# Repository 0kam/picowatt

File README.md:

# picowatt

Raspberry Pi Pico 2 + INA228 による PPK2 ライクな消費電力測定システム。

## クイックスタート

### リリース版を使う(推奨)

1. **ファームウェア**: [Releases](https://github.com/0kam/picowatt/releases) から
   `picowatt-vX.Y.Z.uf2` をダウンロードし、BOOTSEL ボタンを押しながら Pico 2 を
   USB 接続して現れる `RP2350` ドライブにドラッグ(または
   `picotool load -fx picowatt-vX.Y.Z.uf2`)。
2. **PC アプリ**: [uv](https://docs.astral.sh/uv/) があれば1行で起動できる:

   ```sh
   uvx picowatt        # GUI
   uvx --from picowatt picowatt-cli --seconds 10 --csv out.csv
   ```

   (pip 派は `pipx install picowatt` でも可)

### ソースからのビルドと書き込み

必要なもの: cmake、ARM GNU toolchain、[pico-sdk](https://github.com/raspberrypi/pico-sdk) 2.3+(`lib/tinyusb` サブモジュール込み)、picotool 2.3+。

```sh
export PICO_SDK_PATH=~/pico-sdk            # 既定値
export PICO_TOOLCHAIN_PATH=~/toolchains/arm-gnu-toolchain-...  # PATH に無い場合
./firmware/build.sh                        # → firmware/build/picowatt.uf2

# 初回のみ BOOTSEL ボタンを押しながら USB 接続して:
picotool load -fx firmware/build/picowatt.uf2
# 2回目以降はボタン不要(実行中ファームがリブートコマンドを受け付ける)
```

UF2 ドライブへのドラッグ&ドロップでも書き込めるが、USB マスストレージが
制限された環境では picotool 経由(PICOBOOT)が使える。

### PC アプリ

```sh
cd app
uv sync
uv run picowatt        # GUI
uv run picowatt-cli --seconds 10 --csv out.csv   # ヘッドレスキャプチャ
```

GUI: Connect → Start でストリーミング開始。Measure チェックで電力プロット上の
任意区間を選択して Wh/Ah を積算。Log CSV… で全サンプルをファイルに記録。
Calibrate… でゼロ校正・1点ゲイン校正(ボードIDごとに自動保存され、接続時に
自動適用)。プロトコル仕様は [docs/protocol.md](docs/protocol.md)、実測性能は
[docs/verification.md](docs/verification.md) を参照。値がおかしいときは
[docs/troubleshooting.md](docs/troubleshooting.md)（症状から引ける）。

## 概要

INA228 電力モニタを Pico 2 で読み取り、USB シリアル経由で PC に転送。PC 側アプリでリアルタイム表示・ロギング・任意区間の電力量(Wh)積算を行う。

対応する測定モード:

- **消費電力測定** — 機器の消費電力を INA228 1枚で測定
- **DC-DC 効率測定** — INA228 2枚で入出力を同時測定し、効率を算出

## ハードウェア構成

| 役割 | 型番 | 備考 |
|---|---|---|
| MCU | Raspberry Pi Pico 2 (RP2350) | USB CDC で PC 接続 |
| 電力モニタ | Adafruit INA228 ×2 | 15mΩ 0.1% シャント搭載、20bit ADC |
| ディスプレイ | SSD1306 128×64 I2C OLED | 秋月 |
| 電源 | アズワン PS30V5A10 | 0-30V / 0-5A |
| 電子負荷 | ET5410A+ | 効率測定時の負荷掃引用 |

### I2C アドレス

| デバイス | アドレス | 設定 |
|---|---|---|
| SSD1306 OLED | `0x3C` | — |
| INA228 #1 (入力側) | `0x40` | デフォルト |
| INA228 #2 (出力側) | `0x41` | 基板裏 A0 ジャンパを閉 |

### 結線

ロジック側は I2C0 バスに全デバイスをぶら下げる。ブレッドボード配線の代わりに
キャリア基板を起こす場合は [hardware/](hardware/README.md) を参照(KiCad プロジェクト)。

| Pico 2 | 接続先 |
|---|---|
| 3V3 OUT (pin 36) | INA228 ×2 VIN / OLED VCC |
| GND (pin 38) | INA228 ×2 GND / OLED GND / 電源 − (1点のみ) |
| GP4 (pin 6) SDA | INA228 ×2 SDA / OLED SDA |
| GP5 (pin 7) SCL | INA228 ×2 SCL / OLED SCL |

I2C プルアップは INA228 基板の 10kΩ が効くため追加不要。

ブレッドボードで組む場合の全体図（ロジック配線 + 電源経路）:

電力ラインはハイサイド測定。**基板裏の VBus ジャンパを閉じる**(VBUS が VIN+ に接続され、ハイサイド構成になる)。

```
電源(+) → #1 VIN+ ─[15mΩ]─ #1 VIN− → DUT(+)
電源(−) ←──────────────────────────── DUT(−)
```

キャリア基板でのつなぎ方（赤 = ＋側、青 = −側。USB が左、端子台が上辺）:

効率測定時は出力側に #2 を追加:

```
DUT出力(+) → #2 VIN+ ─[15mΩ]─ #2 VIN− → 電子負荷(+)
DUT出力(−) ←───────────────────────────── 電子負荷(−)
```

ch1 用の INA228 は裏の A0 ジャンパを閉じて右の J3 に挿す。詳細は
[hardware/README.md](hardware/README.md#使い方配線図)。

**電源の − は必ず picowatt の GND（キャリア基板なら J5）に繋ぐ。** INA228 は
バス電圧を自分の GND ピン基準で測るので、この 1 本が無いと基板が電源系から
浮き、VBUS が 0 V と −数十 V の間を 50/60 Hz で振動する（実在しない電圧）。
GUI はステータスバー右端に赤字の警告を出し、`picowatt-cli` は
`WARNING: bus voltage goes negative` を出す。図解は [docs/troubleshooting.md](docs/troubleshooting.md)。

GND の共通接続は 1 点のみ。複数箇所で接続するとループになる。

## キャリブレーション

INA228 は `SHUNT_CAL` レジスタ (0x02) にシャント値とフルスケールから決まる係数を書き込む必要がある。

```
CURRENT_LSB = 最大期待電流 / 2^19
SHUNT_CAL   = 13107.2e6 × CURRENT_LSB × R_SHUNT
```

`R_SHUNT = 0.015` (Adafruit ボード搭載値)。

デフォルト設定 (3A 想定, ADCRANGE=0 / ±163.84mV):

```
CURRENT_LSB = 8e-6        # 8 µA/LSB, フルスケール約 4.19A
SHUNT_CAL   = 1573
```

低電流モード (ADCRANGE=1 / ±40.96mV) では CURRENT_LSB を 1/4 に下げて分解能を上げる。
ADCRANGE=1 では **SHUNT_CAL の計算値を 4 倍**する必要があるが、LSB の 1/4 と相殺して
レジスタ値は同じになる:

```
CURRENT_LSB = 2e-6        # 2 µA/LSB, フルスケール約 1.05A
SHUNT_CAL   = 1573        # = 4 × 13107.2e6 × 2e-6 × 0.015
```

出荷時のシャント実値は公称から数%ずれることがあるため、既知電流での 1 点校正を推奨。

## 機能要件

### ファームウェア (Pico 2)

- INA228 ×2 の初期化・設定変更 (ADCRANGE, 変換時間, 平均化回数)
- 定期サンプリングと USB シリアルへのストリーミング
- OLED へのリアルタイム数値表示
- PC からのコマンド受信 (レンジ切替、サンプリングレート変更、ゼロ校正、モード切替)
- I2C は 400kHz 以上 (Pico 2 は 1MHz まで可)

### PC アプリ

- シリアル接続とリアルタイムグラフ表示 (電圧 / 電流 / 電力)
- CSV ロギング
- **表示中の任意範囲を選択して電力量(Wh)を積算**
- 効率モード時は入出力電力と効率(%)を同時表示
- 測定設定の変更 UI

## 想定サンプリングレート

I2C 経由のため PPK2 (100kSa/s) 相当は狙わない。数百 Hz〜数 kHz を目標。変換時間と平均化回数の設定でノイズと速度をトレードオフする。

## 参考

- [Adafruit INA228 Learn Guide](https://learn.adafruit.com/adafruit-ina228-i2c-power-monitor)
- INA228 データシート (TI)

## ライセンス

GPL-3.0 — 詳細は [LICENSE](LICENSE) を参照。

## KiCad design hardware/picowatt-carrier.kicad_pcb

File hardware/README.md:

# picowatt キャリア基板

Pico 2 + INA228 ×2 + SSD1306 OLED を 1 枚に載せるキャリア基板。ロジックはすべて
I2C0 にぶら下がるだけなので、この基板は **電源と I2C を配るだけ** で能動素子を持たない。

- 基板サイズ **92 × 70 mm**（2 層、厚さ 1.6mm）。100×100mm 以内なので各社の最安枠に収まる
- 子基板（Pico 2 / INA228 ×2 / OLED）はすべて 2.54mm ソケットで着脱可能
- 高さはすべて **11.0mm の同一面** に揃う（ソケットのハウジング高さ 8.5mm +
  ピンヘッダのハウジング厚み 2.5mm、いずれも秋月の仕様値）

KiCad 10 で `picowatt-carrier.kicad_pro` を開く。シンボルとフットプリントのうち
本基板固有のものは `picowatt.kicad_sym` / `picowatt.pretty/` にプロジェクト内蔵。
残りは KiCad 標準ライブラリを参照する。

> KiCad を一度も起動していない環境ではグローバルライブラリテーブルが未作成のため、
> 標準ライブラリ参照がエラーになる。KiCad を一度起動すれば自動生成される。

## 配置の考え方

配線の向きを 3 方向に分離してある。

| 方向 | 出ていくもの |
|---|---|
| 上辺（奥） | INA228 ×2 のネジ端子台、GND 端子台 — 太い電源線はすべて奥へ |
| 左辺 | Pico 2 の Micro-USB B — PC へ |
| 手前 | OLED の表示面 |

INA228 の端子台が基板の外を向くので、電源線は基板の上を這わない。

J5 (GND 端子台) も同じ向きに揃えるため **180° 回転して配置してある。** TB007-508 の
機械図面 (SECTION A-A) では、ピン列は電線挿入面ではなく**背面から 4.90mm**（挿入面からは
5.35mm）の位置にある。回転 0 のままだと電線が手前から入り、基板の上をまたぐことになる。

## 回路

ネットは 6 本だけ。

| ネット | 接続先 |
|---|---|
| `+3V3` | Pico 2 pin36 (3V3 OUT) → INA228 ×2 の VIN、OLED VDD、プルアップ、パスコン |
| `GND` | Pico 2 の GND 群、各子基板 GND、GND 端子台、TP1 |
| `SDA` | Pico 2 GP4 (pin 6) → INA228 ×2、OLED |
| `SCL` | Pico 2 GP5 (pin 7) → INA228 ×2、OLED |
| `ALRT0` | Pico 2 GP6 (pin 9) → INA228 ch0 の ALRT |
| `ALRT1` | Pico 2 GP7 (pin 10) → INA228 ch1 の ALRT |

`ALRT0` / `ALRT1` は現ファームウェアでは未使用だが、`firmware/src/config.h` が
GP6/GP7 を予約済みで配線コストがゼロなので引いてある。INA228 側の ALRT は
オープンドレインなのに基板上にプルアップが無いため、R1/R2 (10kΩ) を本基板に載せる。

I2C プルアップは INA228 が各 10kΩ を持ち、2 枚並列で 5kΩ、さらに OLED モジュール分も
乗るので追加不要と判断した。R3/R4 は**未実装** (DNP) のパッドとして用意してあるだけで、
1MHz で波形が鈍る場合にのみ実装する。

### 電力ラインは基板に通さない

INA228 の 2.54mm ヘッダには `VBUS` / `VIN-` / `VIN+` も出ているが、**基板側は無接続**に
してある（J2/J3 の pin 5,6,7）。最大 5A の電力ラインをキャリア基板に通す理由がないため、
電源線は従来通り INA228 自身のネジ端子台に接続する。

> **注意**: 無接続とはいえ、このパッドには測定対象の電源電位（最大 30V）が乗る。
> シルクにも警告を入れてある。

## 部品表

Pico 2 / INA228 ×2 / OLED 以外はすべて秋月電子で揃う。**通販コードと寸法は商品ページで
実際に確認済み**（確認できなかった項目は末尾に明記）。

### 基板に実装するもの

| 通販コード | 品名 | 型番 | 単価 | 入数 | 必要 | Ref / 適合確認 |
|---|---|---|---|---|---|---|
| [103077](https://akizukidenshi.com/catalog/g/g103077/) | ピンソケット(メス) 1×20 | FH-1x20 | ¥50 | 1個 | 2 | J1。ピッチ2.54 / 高さ8.5mm |
| [103785](https://akizukidenshi.com/catalog/g/g103785/) | ピンソケット(メス) 1×8 | FH-1x8SG/RH | ¥30 | 1個 | 2 | J2,J3。高さ8.5mm |
| [110099](https://akizukidenshi.com/catalog/g/g110099/) | ピンソケット(メス) 1×4 | FH-1x4SG/RH | ¥20 | 1個 | 1 | J4。高さ8.5mm |
| [102333](https://akizukidenshi.com/catalog/g/g102333/) | ターミナルブロック 2P 緑 縦 小 | — | ¥35 | 1個 | 1 | J5。**5.08mmピッチ・水平引出し・ねじ式** |
| [125103](https://akizukidenshi.com/catalog/g/g125103/) | カーボン抵抗 1/4W 10kΩ | RD25S | ¥100 | 1袋100本 | 1袋 | R1,R2。立て実装 |
| [125222](https://akizukidenshi.com/catalog/g/g125222/) | カーボン抵抗 1/4W 2.2kΩ | CF25J2K2B | ¥150 | 1袋100本 | 1袋 | R3,R4。**未実装なので省略可** |
| [117897](https://akizukidenshi.com/catalog/g/g117897/) | 電解コンデンサー 10µF50V ルビコンPX | 50PX10MEFC5X11 | ¥10 | 1個 | 1 | C1。φ5×11mm / **端子間2mm** |
| [110147](https://akizukidenshi.com/catalog/g/g110147/) | 積層セラミックコンデンサー 0.1µF250V X7R | RDER72E104K2K1H03B | ¥25 | 1個 | 1 | C2。**端子間5mm** / 5.5×3.15×4mm |
| [112217](https://akizukidenshi.com/catalog/g/g112217/) | チェック端子 TEST-34 | TEST-34 | ¥15 | 1個 | 1 | TP1。径0.8mm |

小計 **約 ¥585**（2.2kΩ を省けば約 ¥435）。

> C2 を安く済ませたい場合は [112670](https://akizukidenshi.com/catalog/g/g112670/)
> (0.1µF 50V X7R **2.54mm**ピッチ, ¥10) でもよい。基板のパッドは 5mm ピッチなので
> リードを外側へ広げて挿す。小型 MLCC なので実際には問題にならない。

### 子基板側に付けるピンヘッダ

| 通販コード | 品名 | 型番 | 単価 | 必要 | 備考 |
|---|---|---|---|---|---|
| [100167](https://akizukidenshi.com/catalog/g/g100167/) | ピンヘッダー 1×40 | PH-1x40SG | ¥35 | 2 | 切って使う。ハウジング厚み2.5mm |

Pico 2 用に 1×20 ×2、INA228 用に 1×8 ×2 で計 56 ピン。1×40 を 2 本で足りる。
**Pico 2 H（ヘッダ実装済み）を使うなら 1 本でよい。** OLED は多くの場合ヘッダ付属。

### 機構部品

**キャリア側の穴はタップの無い通し穴**（子基板用 φ2.8、四隅 φ3.2）。メス-メスの
スタンドオフを子基板とキャリアで挟み、上下からネジで留める。

**必要な高さは 11.0mm。** ソケットのハウジング高さ 8.5mm + ピンヘッダのハウジング厚み
2.5mm で、どちらも秋月の仕様値。子基板の裏面はキャリア面から 11.0mm に来る。

| 用途 | 通販コード | 品名 | 単価 | 必要 |
|---|---|---|---|---|
| 四隅の脚 | [107313](https://akizukidenshi.com/catalog/g/g107313/) | 六角両メネジ FB3-10 (黄銅 M3 10mm) | ¥30 | 4 |
| 同ネジ | [110329](https://akizukidenshi.com/catalog/g/g110329/) | なべ小ねじ(+) M3×10 | ¥180/10個 | 1袋 |

**M2.5 のスペーサーは秋月では扱っていない**（複数のキーワードで検索して確認）。
子基板用は次のどちらかになる。

- **秋月だけで揃える場合**: [113017](https://akizukidenshi.com/catalog/g/g113017/)
  プラスチックスペーサー M2×10mm ¥20 ×8 +
  [113020](https://akizukidenshi.com/catalog/g/g113020/) なべ小ねじ プラスチック M2×5mm
  ¥10 ×16。M2 は φ2.8 の穴に対して緩いが、スペーサーが厚みを決めるので実用上は問題ない。
  10mm なので 1mm 足りず、ワッシャで詰めるか軽く締める程度にする
- **寸法どおりに揃える場合**: M2.5 メス-メス 11mm を廣杉計器などから調達する

なお子基板は 8pin / 4pin のソケット自体でも保持されるので、**スタンドオフは剛性を上げる
ためのもので必須ではない。** ただし INA228 は端子台をドライバーで締めるため、付けた方がよい。

### 確認していないこと

- `102333` の電線挿入口がフットプリントのどちら向きかは未確認。**J5 は両ピンとも GND なので
  向きは電気的に無関係**で、線を出したい方向に合わせて挿せばよい
- ソケットの推奨実装穴径は 1.02mm、基板の穴は 1.0mm。0.02mm の差はドリル公差の範囲内で、
  一般的な 2.54mm ソケットの実装として標準的な値
- 秋月の在庫状況・価格は 2026-07 時点の商品ページの表示

## 組み立て時の設定

シルクにも印刷してあるが、忘れやすいので再掲。

1. **ソケットとチャンネルの対応**: 左の J2 = ch0 (0x40, 入力側)、右の J3 = ch1
   (0x41, 出力側)。各ソケットの左脇に `ch0 0x40 IN` / `ch1 0x41 OUT` を縦書きで
   印刷してある
2. **ch1 に挿す INA228 は裏の A0 ジャンパを閉じる** → アドレス 0x41
   （ch0 用は開放のまま 0x40）
3. **INA228 ×2 とも裏の VBus ジャンパを閉じる** → ハイサイド測定になる
4. **GND の共通接続は 1 点のみ。** 安定化電源の − は J5 だけに落とす

## 使い方（配線図）

図は実物と同じ向き（USB が左、端子台が上辺）。**赤 = ＋側、青 = −側**。
いずれのモードでも測定電流は INA228 モジュール自身のネジ端子台を通り、
**キャリア基板の信号配線には流れない**（J2/J3 の pin 5-7 は無接続）。

- **J5 の 2 つの口はどちらも GND** で、基板内の両面ベタで繋がっている。
  消費電力測定では DUT の−と電源の−を**別々の口に**挿せばよく、
  線を途中で分岐させる必要はない（2 口間の戻り電流は幅の広いベタを
  約 5mm 通るだけで、サブ mΩ・実害なし）
- 効率測定では電源の−端子に 2 本を共締めする
  （DCDC の IN− を J5 の空き口に挿す形でも同じ）
- **端子台の真ん中のネジ (VBus) には何も繋がない**

### 消費電力測定（INA228 1 枚、ch0 のみ）

INA228 は A0 開放のまま **J2**（左、シルク `ch0 0x40 IN`）に挿す。

### DC-DC 効率測定（INA228 2 枚、ch0 + ch1）

ch1 用の INA228 は裏の A0 を閉じて **J3**（右、シルク `ch1 0x41 OUT`）に挿す。

この結線は **非絶縁 DC-DC**（IN− と OUT− が内部で共通）を前提にしている。
絶縁型を測る場合は ch1 のバス電圧の基準が浮いてしまうので、OUT− 側も
基準電位へ 1 点で接続すること。

### よくある間違い：電源の − を J5 に繋ぎ忘れる

INA228 は VBUS を **自分の GND ピン基準**で測る。GND ピンは基板の GND ベタに
落ちているだけなので、電源の − が J5 に来ていないと基板全体が電源系から浮き、
VBUS が 0 V と −数十 V の間を 50/60 Hz で振動する。電流はそれらしく出るので
気付きにくい。

電源の − から J5 の空き口へ 1 本足せば直る。`picowatt-cli` はこの状態を
`WARNING: bus voltage goes negative` として報告する。他の症状は
[docs/troubleshooting.md](../docs/troubleshooting.md)。

図は `tools/wiring_diagrams.py` が基板と同じ座標データから生成している。

## 配線

2 層、配線 57 本 + ビア 8 個。**未配線 0 件・ERC 0 件**で検証済み
（DRC は後述の回転由来の警告 1 件のみ、実害なし）。

| 層 | 用途 |
|---|---|
| B.Cu | `+3V3` 幹線（Y=42.2mm を横断）+ ベタ GND |
| F.Cu | 信号 4 本 + ベタ GND |

`GND` は両面ベタで配るため配線を持たない。全 GND パッドの導通は、ゾーンを塗った状態で
`pcbnew` の接続性チェックにより確認済み（ベタは分断されていない）。

配線幅は信号 0.3mm、電源 0.4mm。全パッドがスルーホールなので、層をまたぐのは
交差回避の 4 箇所（ビア 8 個）だけ。

### 帯状のレーン構成

バンド（Y 33〜38mm）に 4 本の信号レーンを平行に走らせ、そこから各コネクタへ分岐する。

| ネット | レーン Y | Pico 上側列を抜ける X |
|---|---|---|
| `SDA` | 37.2mm | 13.80mm |
| `SCL` | 36.0mm | 16.34mm |
| `ALRT0` | 34.8mm | 23.96mm |
| `ALRT1` | 33.6mm | 26.50mm |

**Pico 2 の下側列（GP4/5/6/7）から上へ抜けるとき、上側列のパッドの隙間を通している。**
パッド径 1.6mm・ピッチ 2.54mm なのでパッド中心から 1.27mm、銅箔間で 0.32mm 空く。
本基板で最も攻めた箇所だが、各社の下限（0.127mm 程度）に対しては十分な余裕がある。

レーンの上下順は「Pico から抜ける X が左のものほど上のレーン」に揃えてあり、
これにより 4 本の立ち上がりが互いに交差しない。上のレーンを跨がざるを得ない
以下の 4 箇所だけ、B.Cu へ潜って戻している（ビア 2 個 × 4 = 8 個）。

| ネット | X | 跨ぐレーン |
|---|---|---|
| `SCL` | 18.19 | `SDA` |
| `SCL` | 48.19 | `SDA` |
| `ALRT0` | 30.89 | `SCL` と `SDA` |
| `ALRT1` | 60.89 | `SCL` と `SDA` |

### プルアップ抵抗の置き方

R1〜R4 は**配線の通り道の上に直接置いてある**。信号側のパッドは 4 本とも既存の配線上に
乗るので、信号側の引き込み配線は 1 本もない。+3V3 側は裏面に 2.8〜4.2mm のスタブが
3 本あるだけで、R4 は +3V3 の既存配線上に乗るためスタブすら不要。

| Ref | 役割 | 信号側パッドが乗っている配線 |
|---|---|---|
| R1 | `ALRT0` プルアップ | ALRT0 の J2.8 への立ち上がり (X=30.89) |
| R2 | `ALRT1` プルアップ | ALRT1 の J3.8 への立ち上がり (X=60.89) |
| R3 | `SDA` プルアップ (未実装) | SDA の OLED への下り (X=74.81) |
| R4 | `SCL` プルアップ (未実装) | SCL の OLED への下り (X=72.27) |

いずれも配線の途中から分岐する形（直列ではない）なので、**R3/R4 を未実装のままでも
`SDA` / `SCL` は繋がる。**

> 当初は 10.16mm ピッチの抵抗を基板左側に並べていたが、配線してみると信号側パッドが
> 基板左端に来てしまい、先に引いた `SDA` の縦線を必ず跨ぐため層をまたぐ箇所が 5 つ必要になった。
> 2.54mm ピッチの立て実装に変更し、配線経路上へ移動して解消している。

## tools/

この基板は生成スクリプトで作られている。**KiCad ファイルが正であり、これらを再実行すると
上書きされる**ので、レイアウトを作り直すとき以外は触らなくてよい。

| ファイル | 役割 |
|---|---|
| `generate.py` | 部品配置・ネットリスト・ベタ・シルクを含む KiCad プロジェクトを生成 |
| `routes.py` | 配線をキャリア座標のポリラインで定義 |
| `routelib.py` | 基板の読み取り、クリアランス／接続性の事前チェック、配線の書き出し |
| `audit.py` | 保存済み基板から配線を読み直し、実クリアランス余裕を報告 |
| `wiring_diagrams.py` | README 用の配線図 (docs/wiring-*.svg, docs/breadboard-*.svg, docs/vbus-reference.svg) を生成 |

再生成する場合は `generate.py` → `routelib.emit()` → `pcbnew` でゾーン塗り、の順。
`audit.py` は KiCad の DRC とは独立に幾何を検算するので、変更後の確認に使える。

## 発注

2 層・1.6mm・92×70mm。特殊な要求は無いので JLCPCB / PCBWay / Elecrow のいずれでも最安枠。

```sh
kicad-cli pcb export gerbers picowatt-carrier.kicad_pcb -o gerber/
kicad-cli pcb export drill   picowatt-carrier.kicad_pcb -o gerber/
```

## 既知のリスク

**OLED モジュールのロット差。** 秋月 112031 は商品ページに「ロットにより外観が異なります」
と明記されており、秋月が配布している参考 PDF は実物と別基板（PDF は 27.3×27.3mm /
シルク `GND VCC SCL SDA`、実物は 25×27mm / `GND VDD SCK SDA`）。本設計は**実測値**
（外形 25×27mm、取付穴ピッチ 21×23mm、穴径 φ2.75、ヘッダは上辺から 1.5mm）に基づく。

交換品を買う場合は寸法だけでなく **ピンの並び順も必ず確認すること。** この種のモジュールには
`GND` と `VCC` が逆のロットが実在する。取付穴が左右対称 (±10.5mm) なので**逆順品でも機械的には
刺さってしまい、電源を逆接する**。基板は pin1=GND / pin2=VDD 前提。

この事故を防ぐため、**基板のシルクに各パッドのピン名を印刷してある。**

- J4 の 4 パッドの脇に `GND` `VDD` `SCK` `SDA` を縦書きで(モジュールを載せる前、
  はんだ付けの段階で手元のモジュールと突き合わせられる)
- 基板下端に `J4 OLED pin1=GND VDD SCK SDA` を 1 行(モジュール実装後も読める)
- J2/J3 も同様に `VIN GND SCL SDA VBUS VIN- VIN+ ALRT` を各パッド脇に印刷

**回転したフットプリントの `lib_footprint_mismatch` 警告。** J5 は 180° 回転して配置して
あるため、`kicad-cli pcb drc` がこの警告を 1 件出す。回転させたフットプリントであれば
部品を問わず出る kicad-cli 側の比較の癖で（無関係な部品を回して再現確認済み）、
実体は隠しテキストの角度差。製造・機能への影響はない。

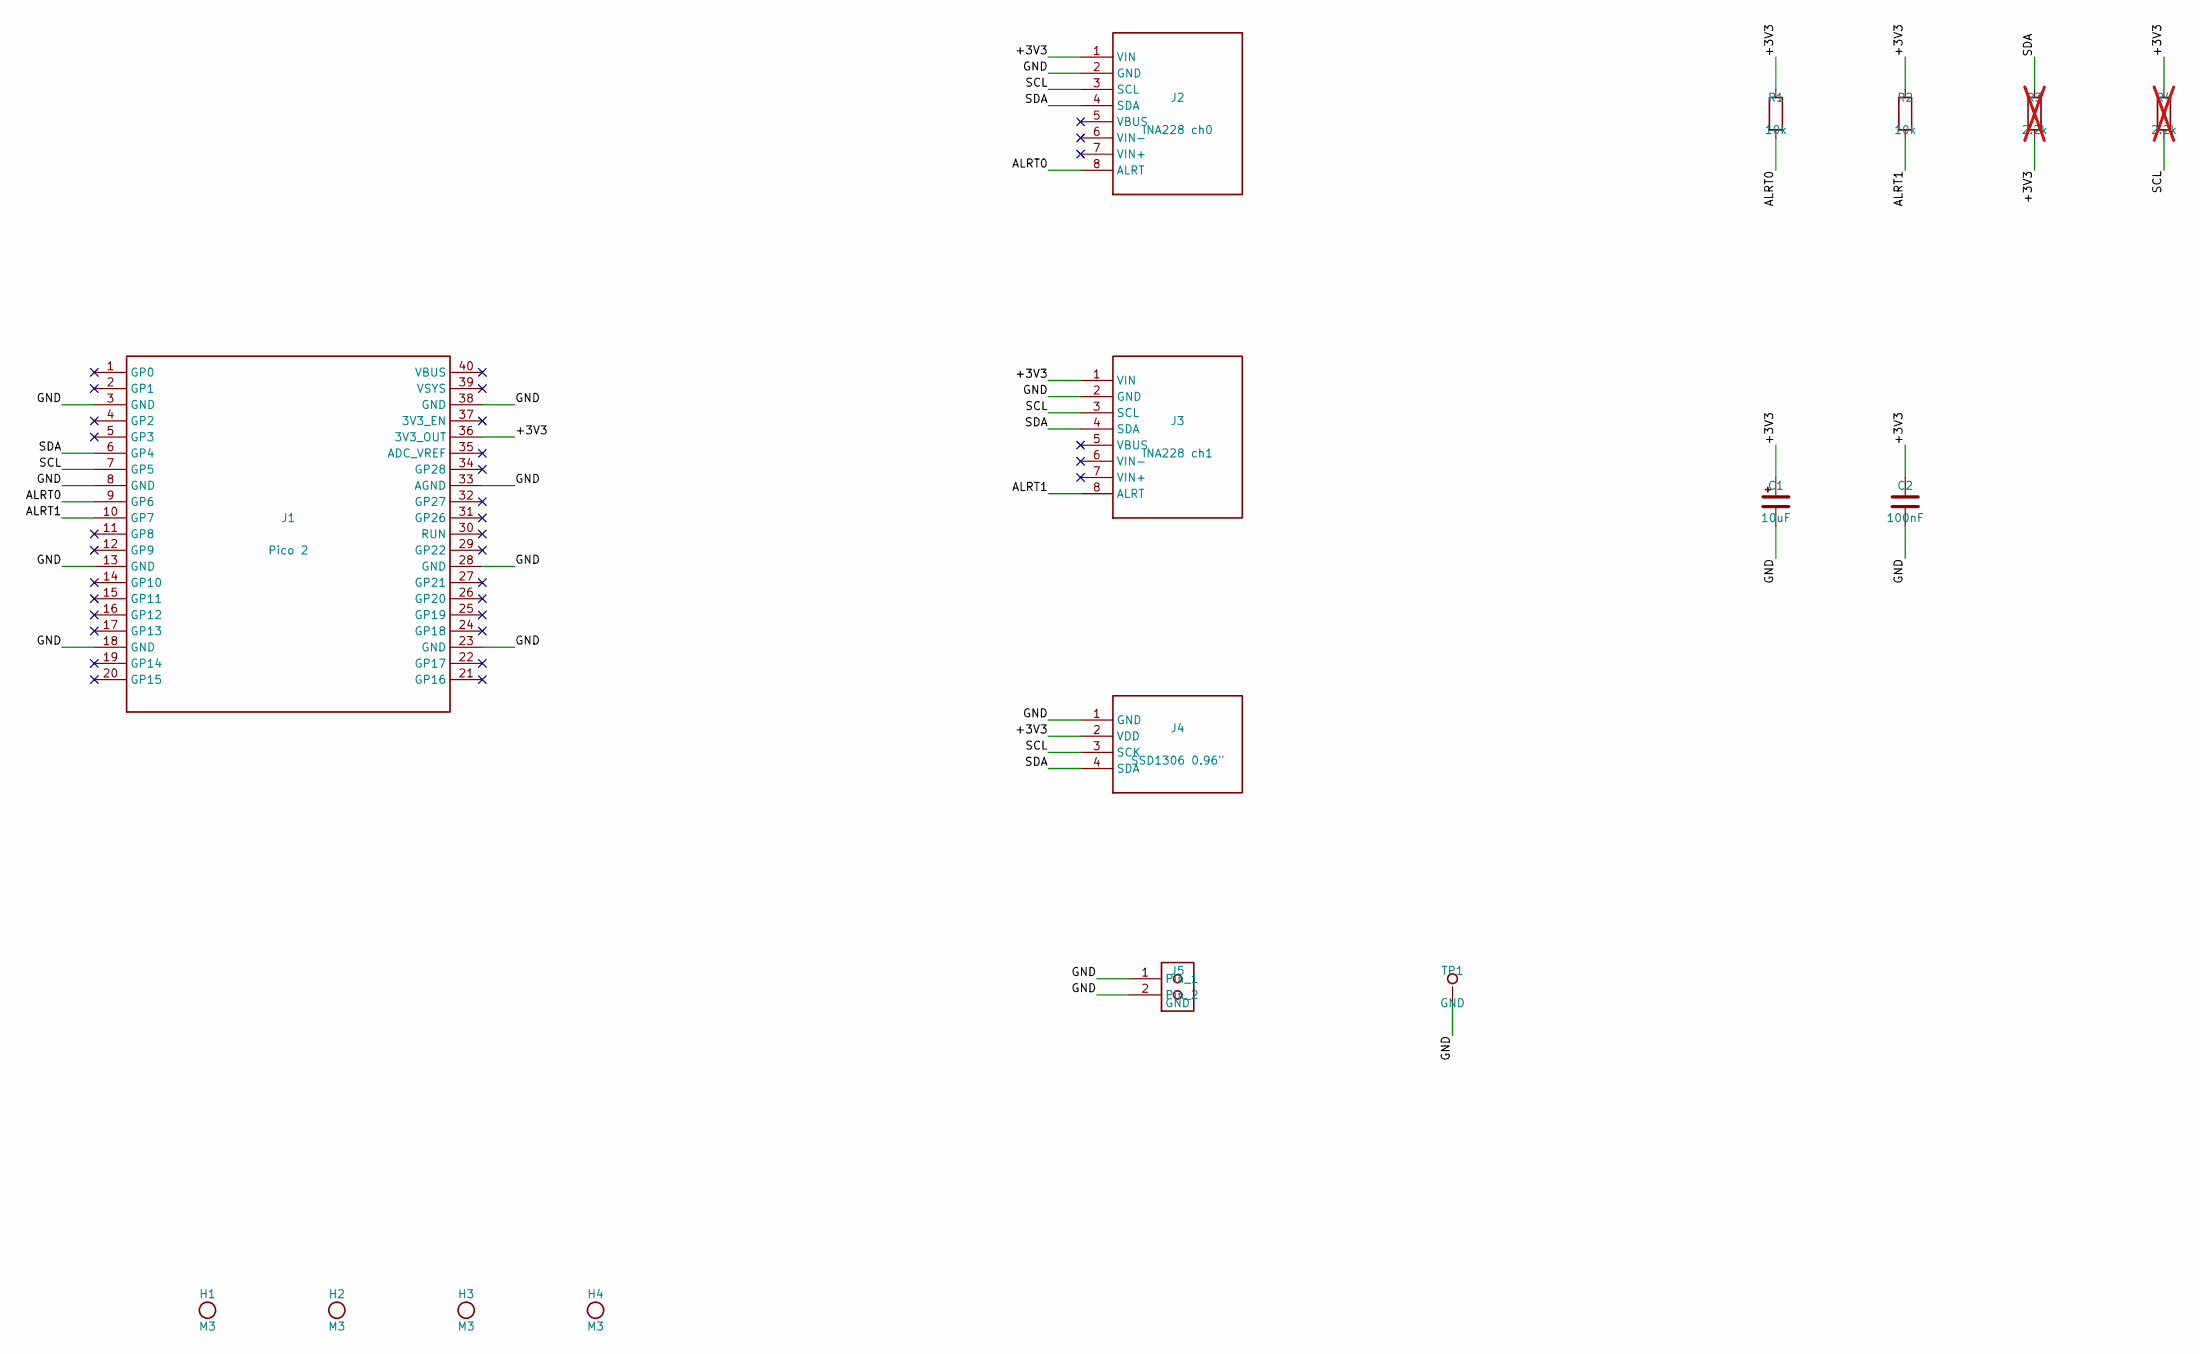
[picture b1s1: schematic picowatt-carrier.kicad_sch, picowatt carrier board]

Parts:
C1: 10uF; CP_Radial_D5.0mm_P2.00mm
C2: 100nF; C_Disc_D5.0mm_W2.5mm_P5.00mm
H1, H2, H3, H4: M3; MountingHole_3.2mm_M3
J1: Pico 2; Pico2_Socket_2x20_P2.54mm
J2: INA228 ch0; INA228_Breakout_Socket_1x08
J3: INA228 ch1; INA228_Breakout_Socket_1x08
J4: SSD1306 0.96"; OLED_SSD1306_Socket_1x04
J5: GND; TerminalBlock_CUI_TB007-508-02_1x02_P5.08mm_Horizontal
R1, R2: 10k; R_Axial_DIN0207_L6.3mm_D2.5mm_P2.54mm_Vertical
R3, R4: 2.2k; R_Axial_DIN0207_L6.3mm_D2.5mm_P2.54mm_Vertical; not fitted
TP1: GND; TestPoint_Loop_D2.50mm_Drill1.0mm

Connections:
/+3V3: C1.1, C2.1, J1.36 (3V3_OUT), J2.1 (VIN), J3.1 (VIN), J4.2 (VDD), R1.1, R2.1, R3.2, R4.1
/ALRT0: J1.9 (GP6), J2.8 (ALRT), R1.2
/ALRT1: J1.10 (GP7), J3.8 (ALRT), R2.2
/GND: C1.2, C2.2, J1.3 (GND), J1.8 (GND), J1.13 (GND), J1.18 (GND), J1.23 (GND), J1.28 (GND), J1.33 (AGND), J1.38 (GND), J2.2 (GND), J3.2 (GND), J4.1 (GND), J5.1, J5.2, TP1.1
/SCL: J1.7 (GP5), J2.3 (SCL), J3.3 (SCL), J4.3 (SCK), R4.2
/SDA: J1.6 (GP4), J2.4 (SDA), J3.4 (SDA), J4.4 (SDA), R3.1

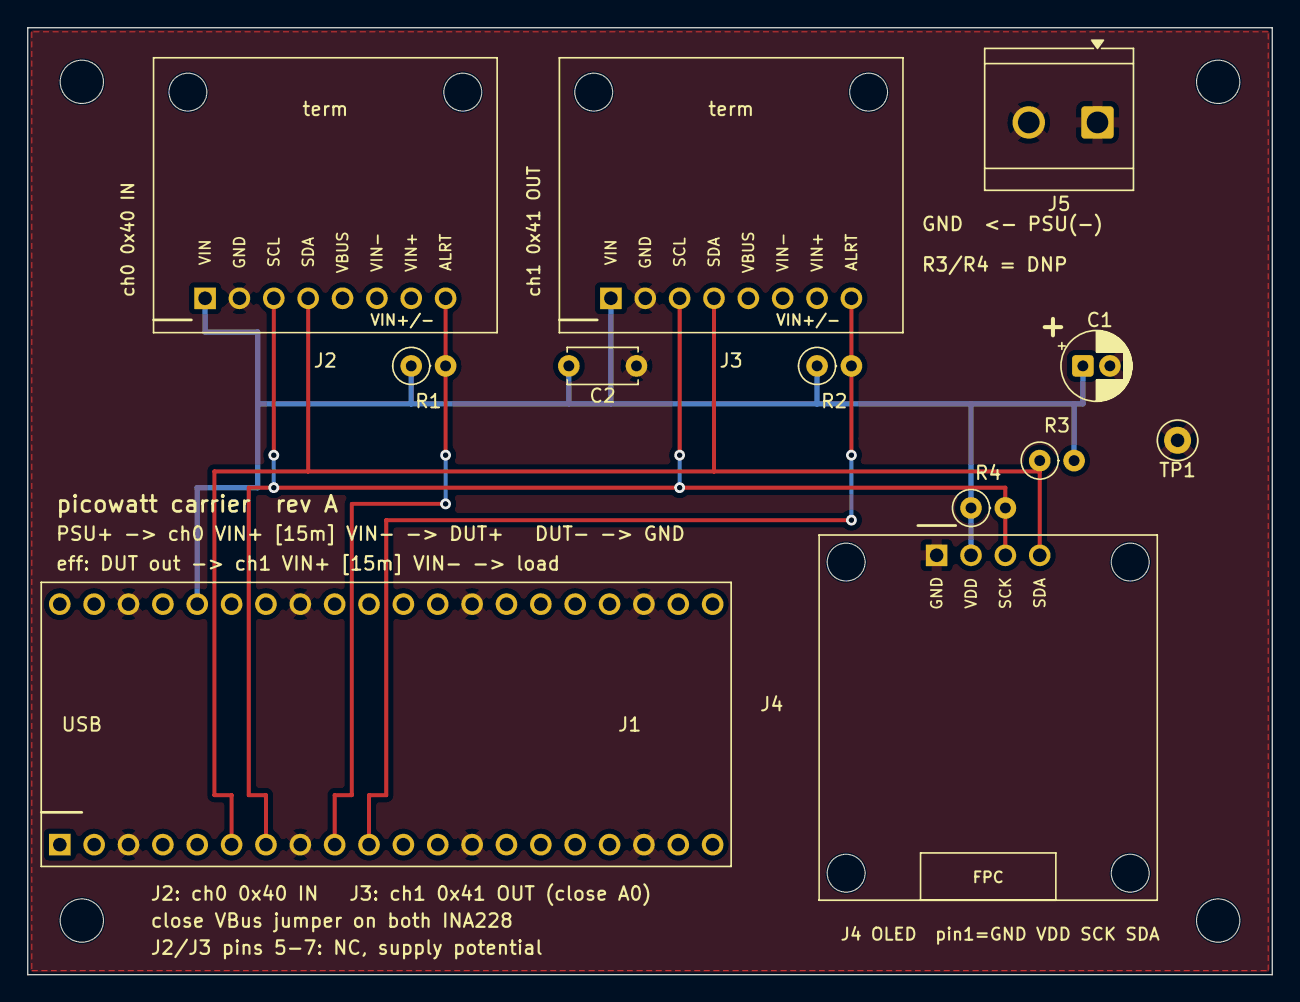
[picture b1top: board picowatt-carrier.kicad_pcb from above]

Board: 2 copper layers, 92.0 x 70.0 mm, 16 parts (0 on the bottom side), 6 nets.
